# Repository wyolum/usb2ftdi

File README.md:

# usb2ftdi
simple converter board to allow micro / mini / B USB input and FTDI output (power only)

License
-------
[CERN Open Hardware Licence v1.2 ]

[CERN Open Hardware Licence v1.2 ]:http://www.ohwr.org/attachments/2388/cern_ohl_v_1_2.txt

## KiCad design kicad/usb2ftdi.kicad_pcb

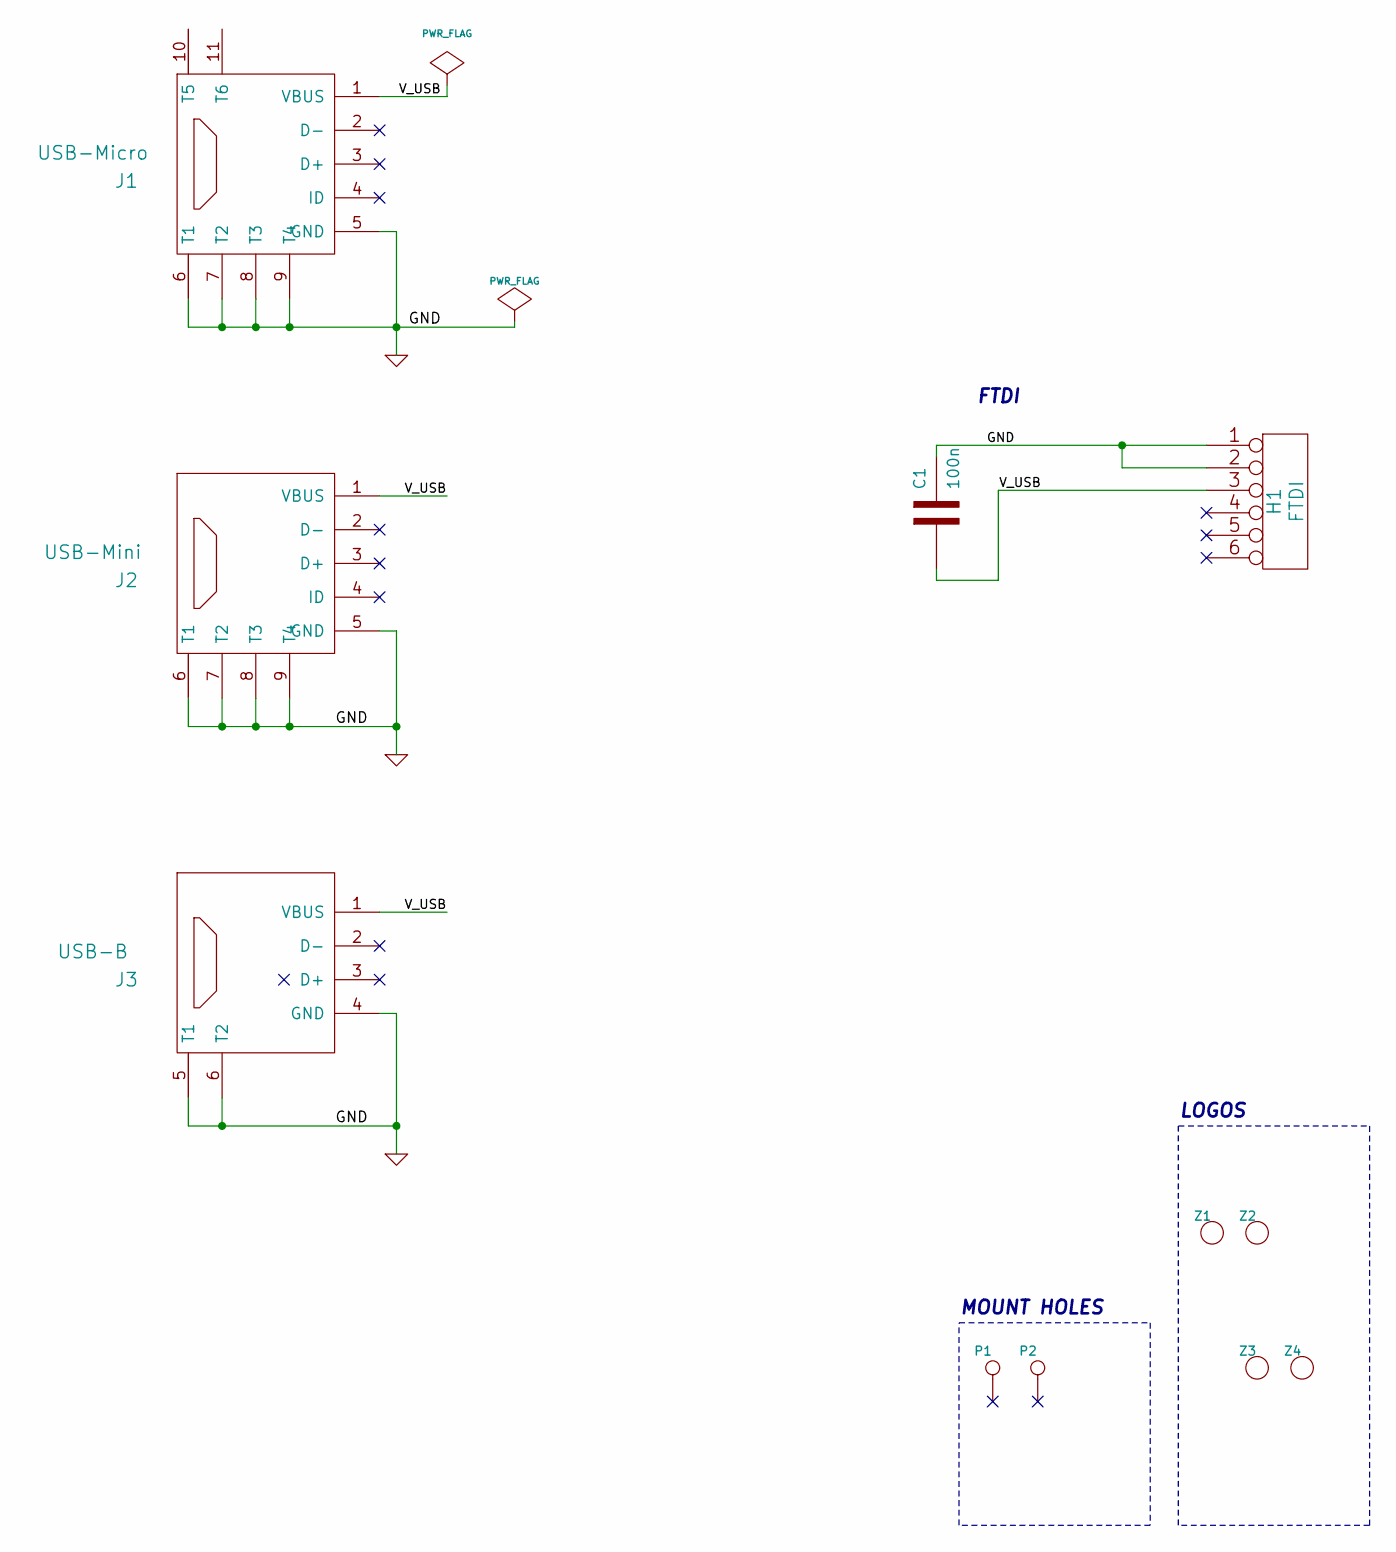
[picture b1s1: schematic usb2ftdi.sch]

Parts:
C1: 100n; Capacitor3MMDiscRM2.5
H1: FTDI; Pin_Header_Angled_1x06
J1: USB-Micro; USB_Micro-B
J2: USB-Mini; USB_Mini-B
J3: USB-B; USB_B
P1, P2: CONN_1; 1pin
Z1, Z2, Z3, Z4: CONN_1; pin_array_1x01

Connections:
/V_USB: C1.1, H1.3, J1.1 (VBUS), J2.1 (VBUS), J3.1 (VBUS)
GND: C1.2, H1.1, H1.2, J1.5 (GND), J1.6 (T1), J1.7 (T2), J1.8 (T3), J1.9 (T4), J1.10 (T5), J1.11 (T6), J2.5 (GND), J2.6 (T1), J2.7 (T2), J2.8 (T3), J2.9 (T4), J3.4 (GND), J3.5 (T1), J3.6 (T2)

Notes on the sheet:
FTDI
MOUNT HOLES
LOGOS

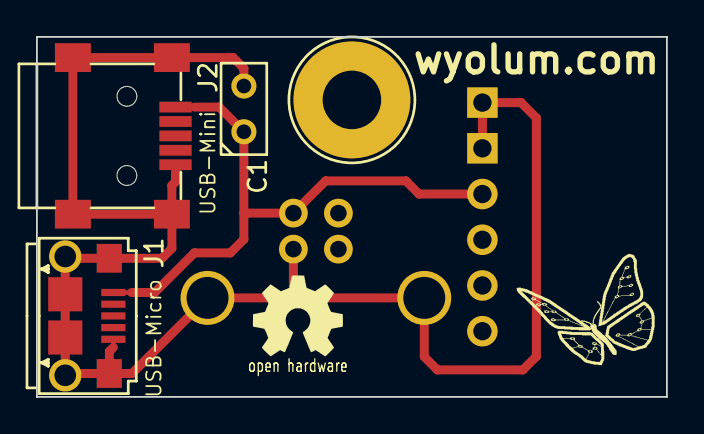
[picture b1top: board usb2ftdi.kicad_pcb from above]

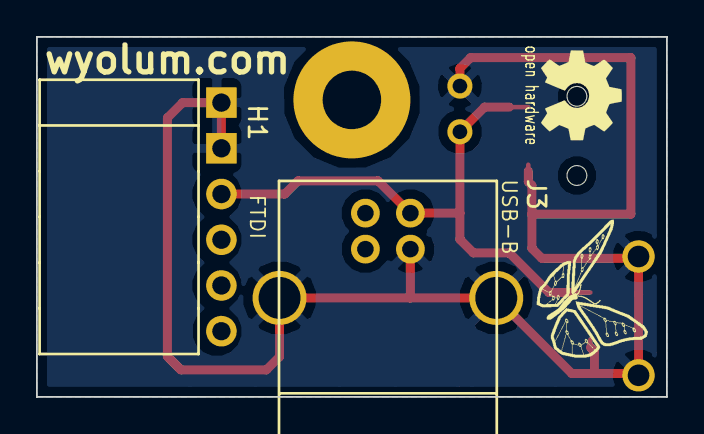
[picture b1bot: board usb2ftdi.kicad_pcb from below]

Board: 2 copper layers, 35.0 x 20.0 mm, 10 parts (4 on the bottom side), 2 nets.

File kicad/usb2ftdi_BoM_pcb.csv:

"Id";"Designator";"Package";"Quantity";"Designation";"Supplier and ref";
1;"J2";"USB_Mini-B";1;"USB-Mini";;;
2;"Z4,Z3";"Logo_silk_OSHW_6x6mm";2;"CONN_1";;;
3;"Z2,Z1";"Logo-WL3";2;"CONN_1";;;
4;"P1";"Screw_3mm";1;"CONN_1";;;
5;"J1";"USB_B_Micro";1;"USB-Micro";;;
6;"C1";"C1";1;"100n";;;
7;"H1";"Socket_Strip_Angled_1x06";1;"FTDI";;;
8;"J3";"USB_B";1;"USB-B";;;

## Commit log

2015-01-31 initialized
2015-01-31 layout in progress
2015-02-01 complete, ready to order
